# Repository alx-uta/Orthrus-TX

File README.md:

# Orthrus-TX

OrthrusTx is a custom high-performance RC transmitter platform built around the STM32H745 microcontroller and designed specifically for modern ExpressLRS-based systems. The project focuses on low-latency control, clean mixed-signal hardware design, modular RF integration, and long-term expandability without unnecessary complexity.

The hardware architecture separates critical analog, digital, and RF sections across an 8-layer PCB stackup to improve signal integrity and reduce noise coupling.

## Features

- STM32H745ZIT6 dual-core MCU
- Dual independent ExpressLRS interfaces
- Modular RF daughterboard design
- Precision filtered analog joystick inputs
- USB connectivity
- SD card support
- Rotary encoders and configurable inputs
- Dedicated analog and digital power domains
- Low-noise mixed-signal PCB layout
- Replaceable battery-oriented design

## Design Goals

OrthrusTx prioritizes:

- Low latency
- High reliability
- Electrical cleanliness
- Modular hardware architecture
- Repairability

## Project Vision

OrthrusTx is being developed both as a functional long-range RC transmitter and as a deep embedded hardware/software engineering project focused on performance, architecture, signal integrity, and system-level design.

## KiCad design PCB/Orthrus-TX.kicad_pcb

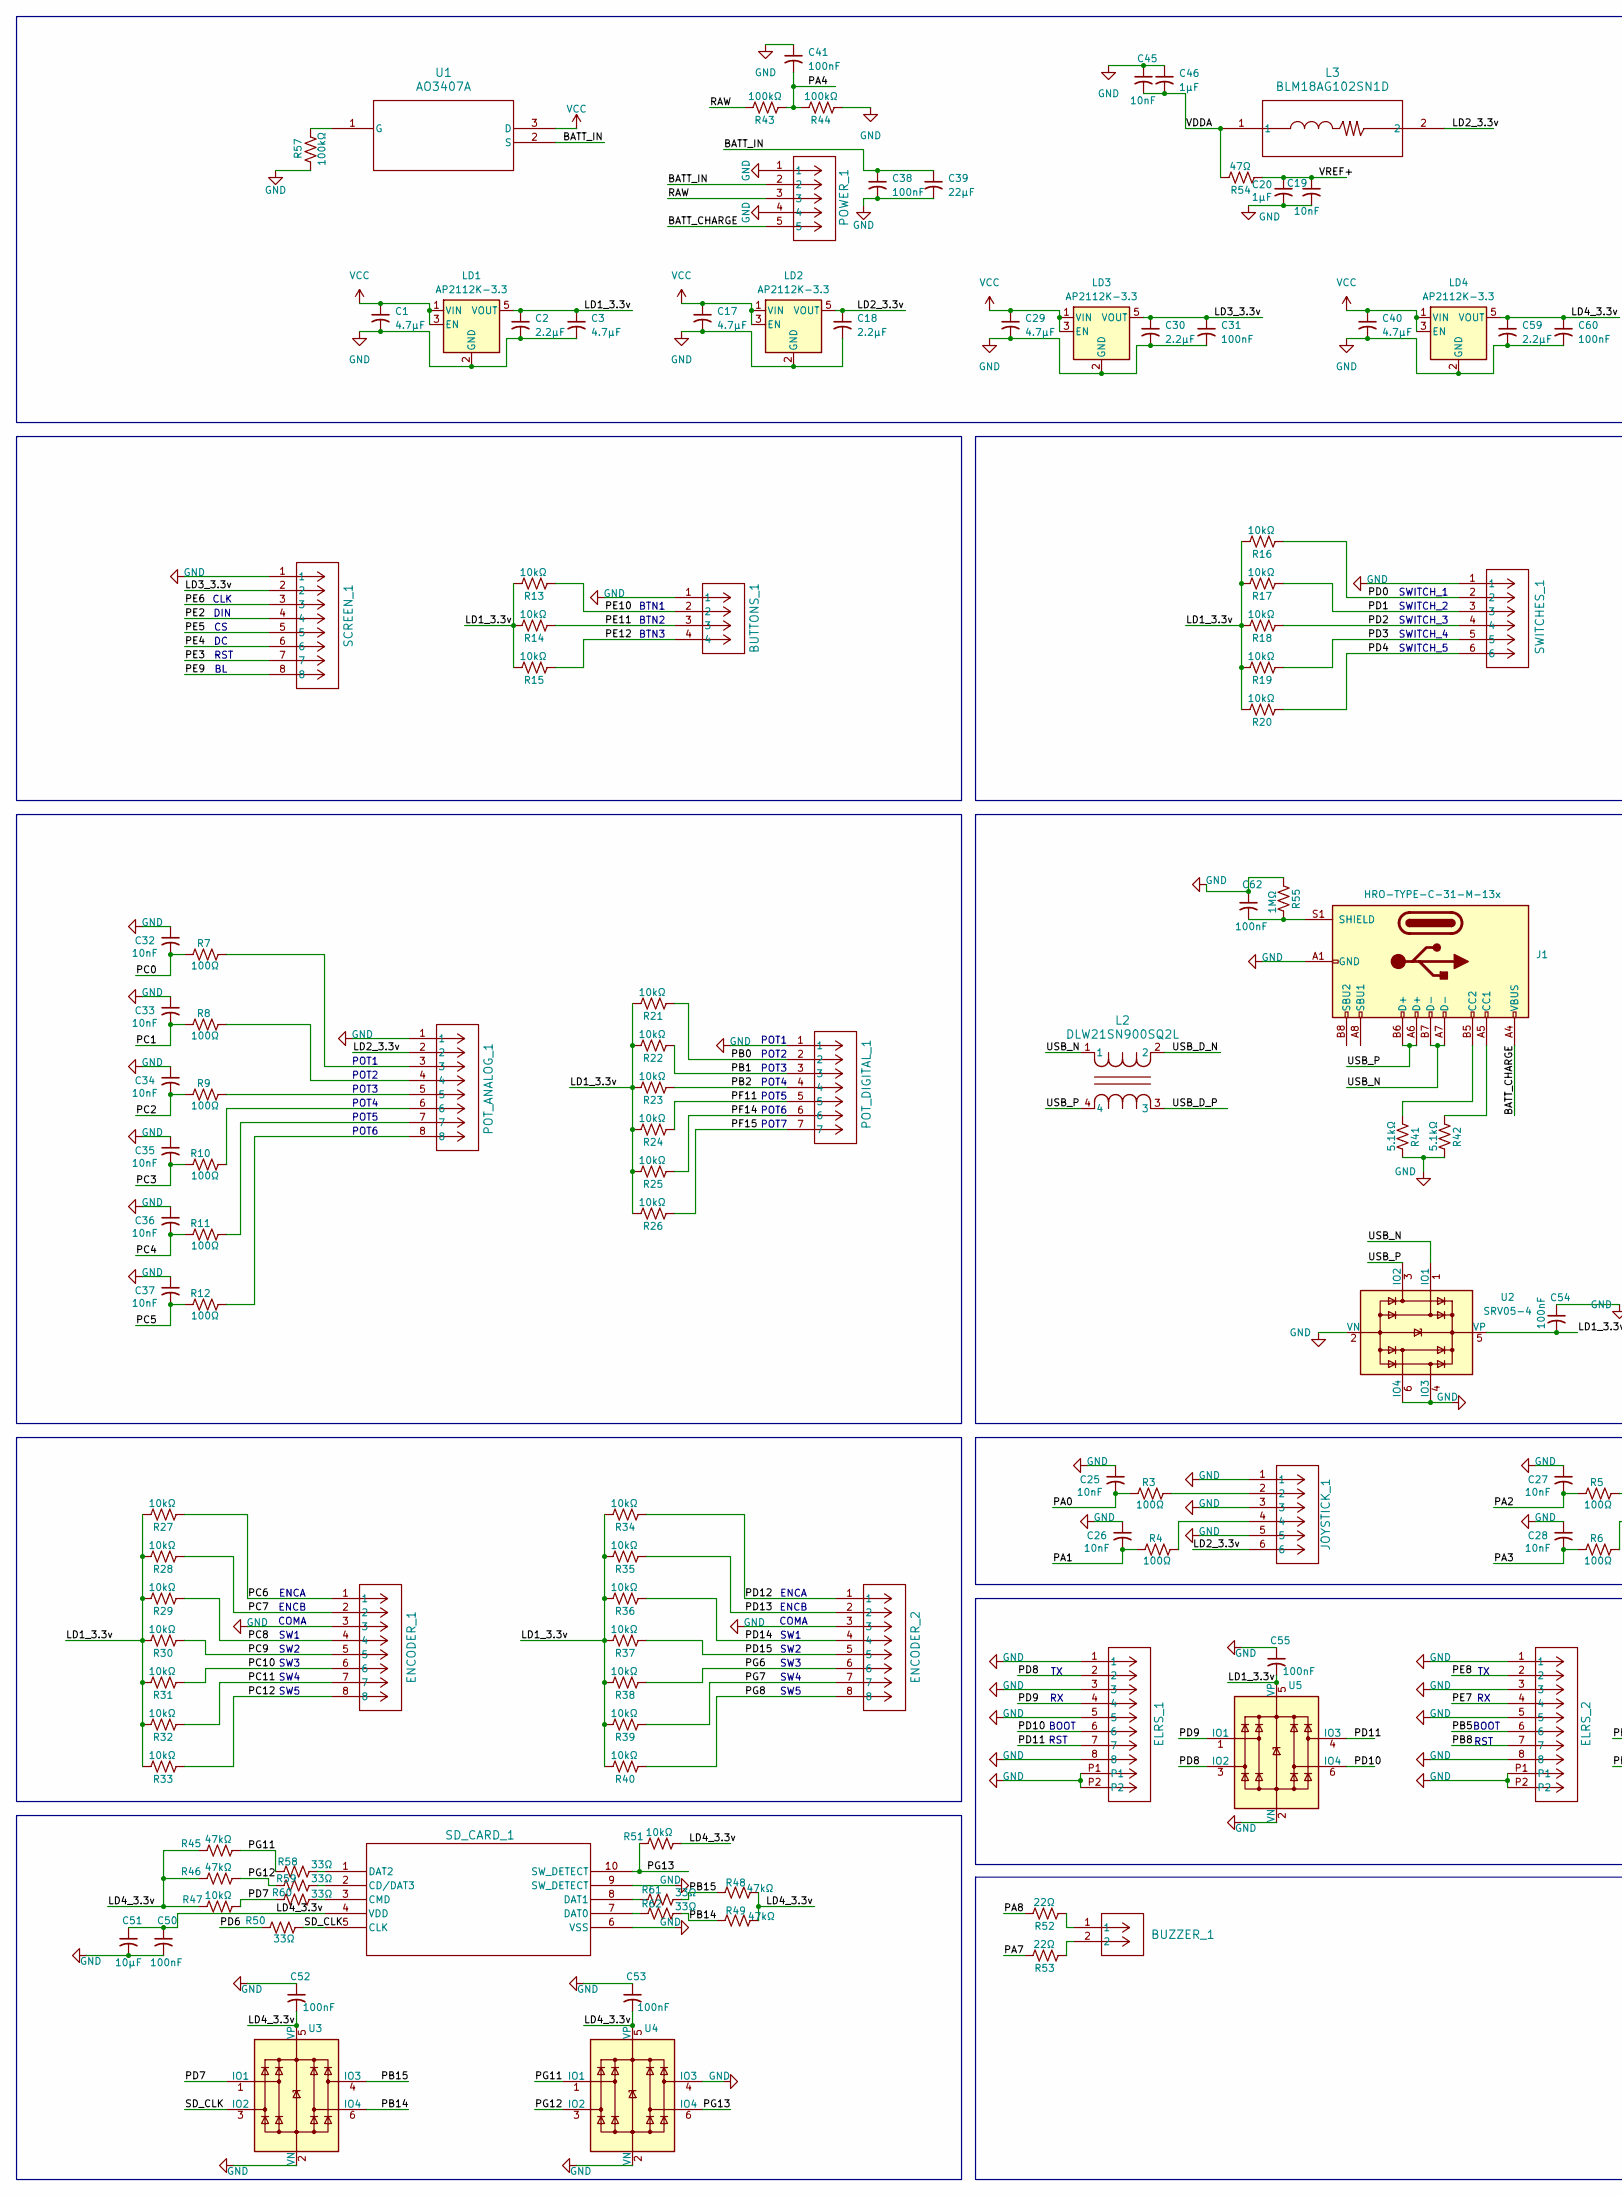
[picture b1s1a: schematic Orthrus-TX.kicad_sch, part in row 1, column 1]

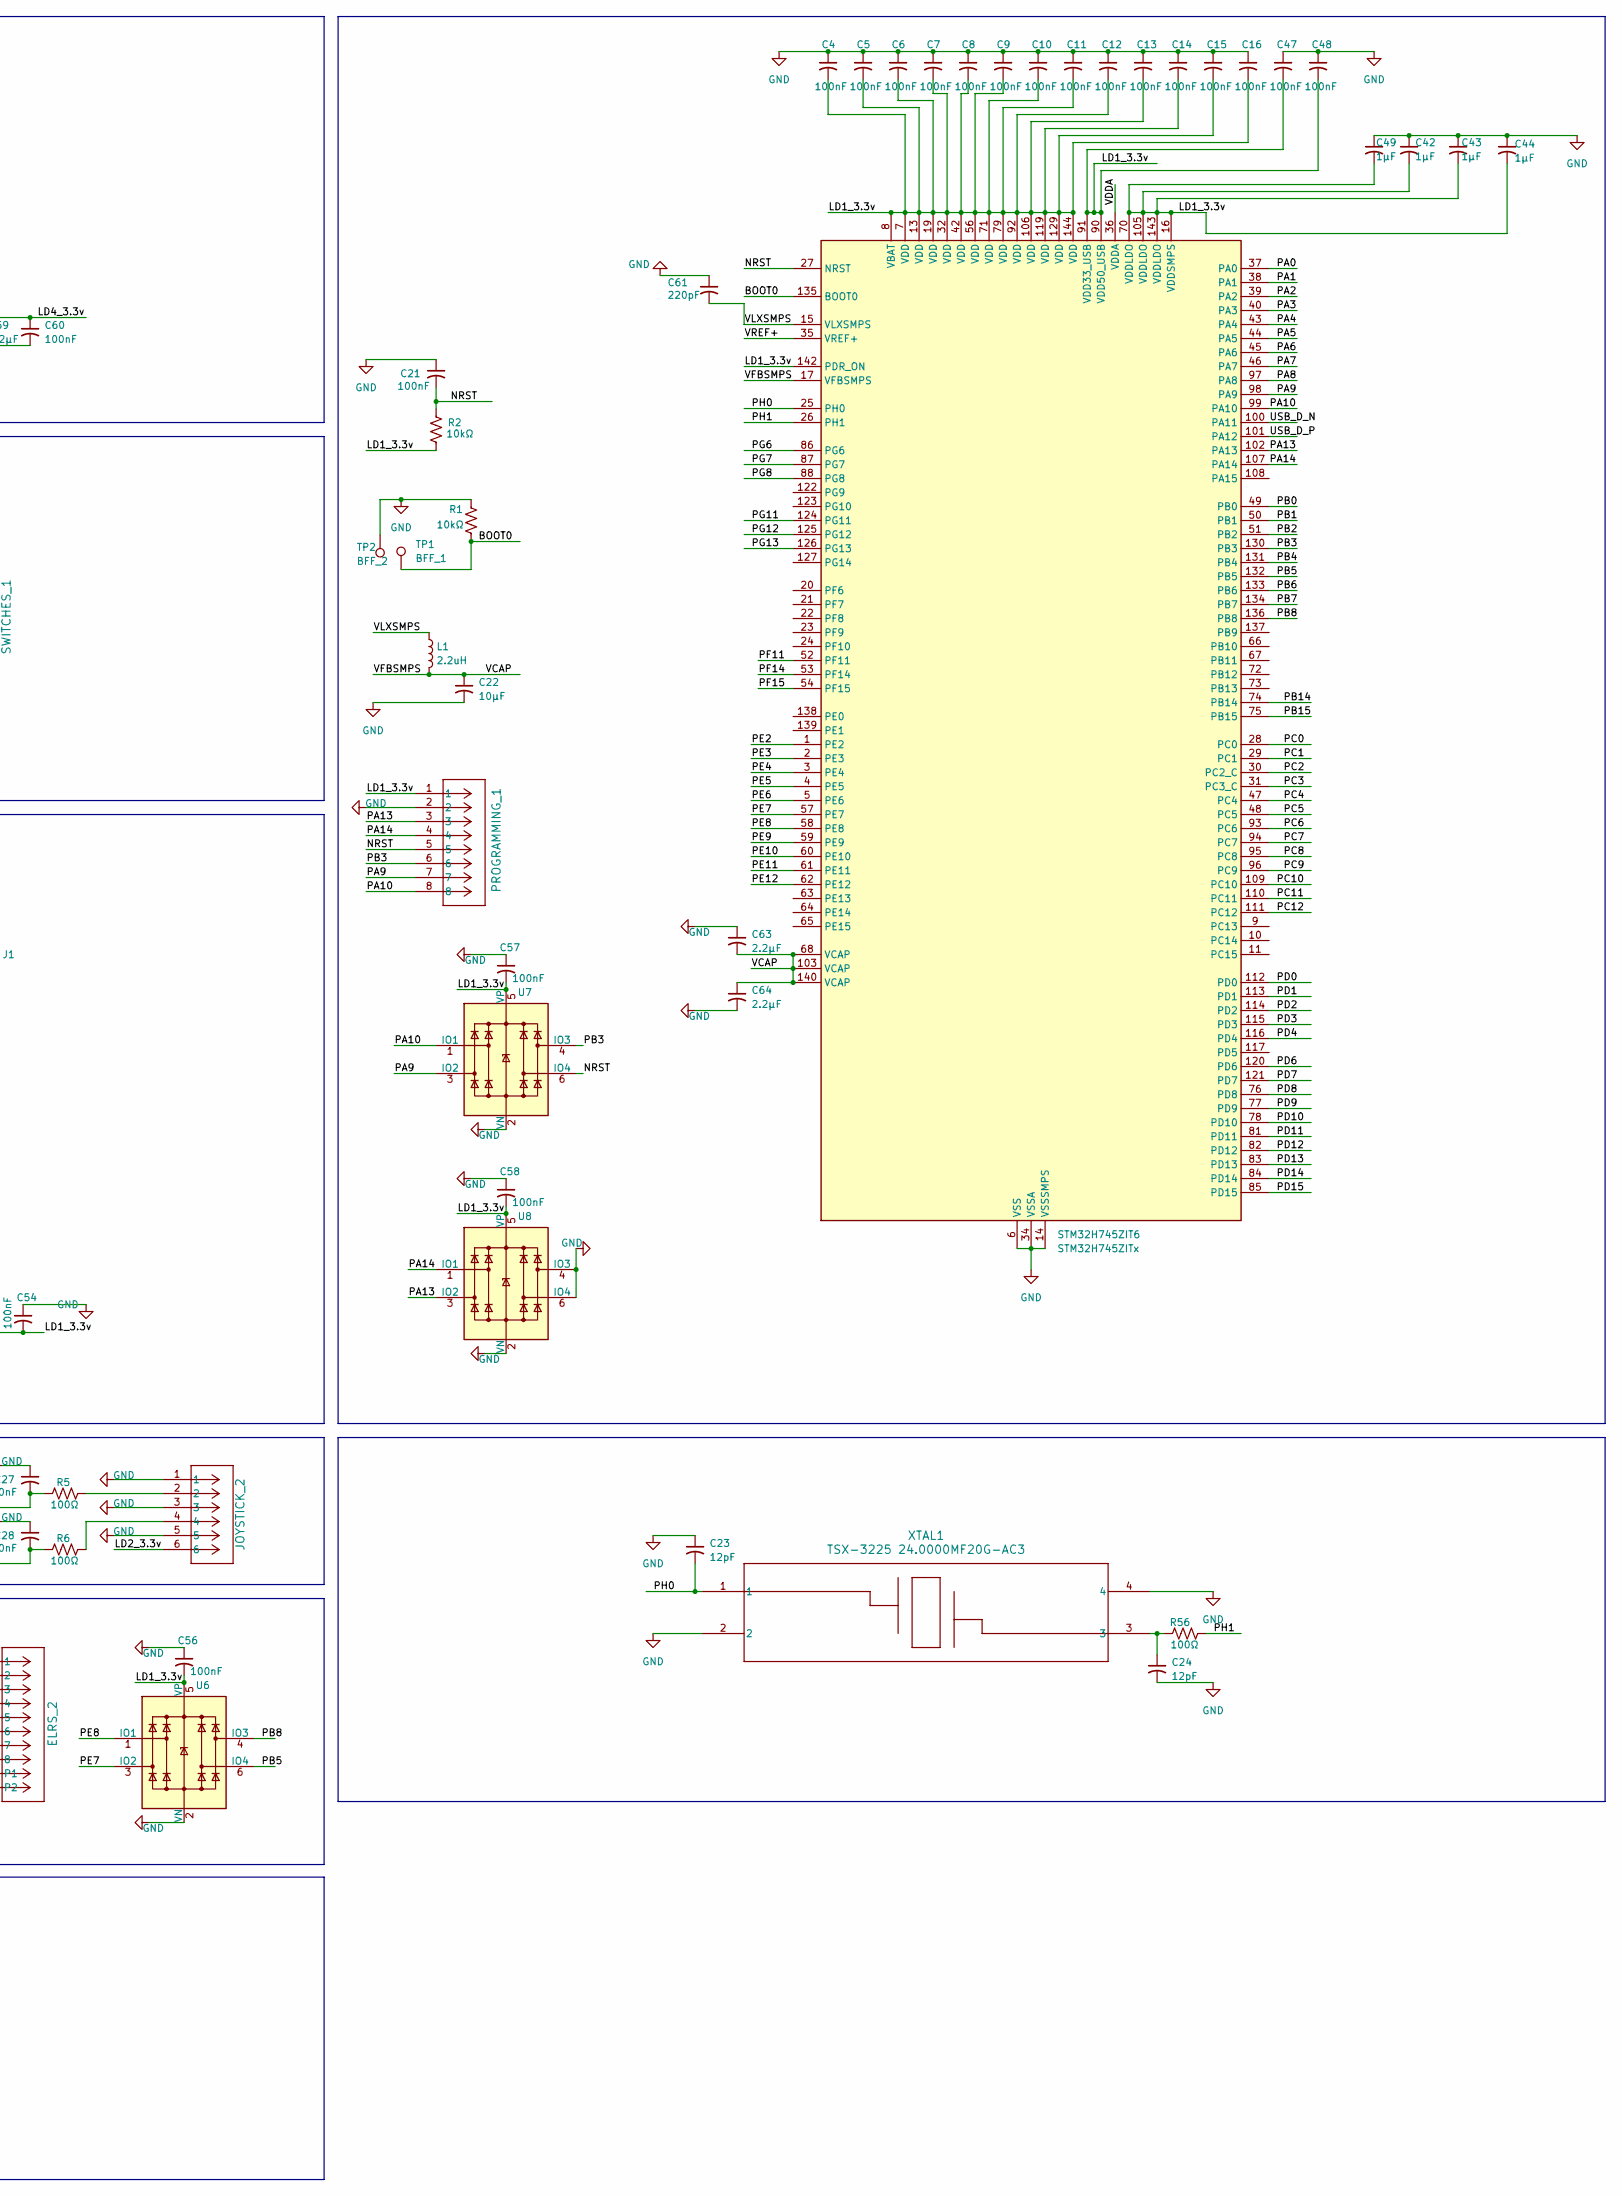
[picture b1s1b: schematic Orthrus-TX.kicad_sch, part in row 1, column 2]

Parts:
BUTTONS_1: 532610471; CONN_532610001-SD_04_MOL; LCSC C696092
BUZZER_1: 532610271; CONN_532610001-SD_02_MOL; LCSC C177225
C1, C3, C17, C29, C40: 4.7µF; C_0603_1608Metric; LCSC C19666
C2, C18, C30, C59, C63, C64: 2.2µF; C_0603_1608Metric; LCSC C23630
C4, C5, C6, C7, C8, C9, C10, C11, C12, C13, C14, C15, C16, C21, C31, C38, C41, C47, C48, C50, C52, C53, C54, C55, C56, C57, C58, C60, C62: 100nF; C_0603_1608Metric; LCSC C24452
C19, C25, C26, C27, C28, C32, C33, C34, C35, C36, C37, C45: 10nF; C_0603_1608Metric; LCSC C3836718
C20, C42, C43, C44, C46, C49: 1µF; C_0603_1608Metric; LCSC C2177011
C22, C51: 10µF; C_0603_1608Metric; LCSC C19702
C23, C24: 12pF; C_0603_1608Metric; LCSC C882527
C39: 22µF; C_0603_1608Metric; LCSC C2762594
C61: 220pF; C_0603_1608Metric; LCSC C882575
ELRS_1, ELRS_2: 5034800800; CON_5034800800_MOL; LCSC C293338
ENCODER_1, ENCODER_2: 532610871; CONN_532610001-SD_08_MOL; LCSC C293349
J1: HRO-TYPE-C-31-M-13x; Molex-216990_GCT-USB45xx_HRO-TYPE-C-31-M-13x-PiMicro_1_DOUB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; LCSC C963373
JOYSTICK_1, JOYSTICK_2: 532610671; CONN_532610001-SD_06_MOL; LCSC C17393620
L1: 2.2uH; L_0603_1608Metric; LCSC C48945021
L2: DLW21SN900SQ2L; IND_DLW21S_0805_MUR; LCSC C97856
L3: BLM18AG102SN1D; BLM18_MUR; LCSC C85824
LD1, LD2, LD3, LD4: AP2112K-3.3; SOT-23-5; LCSC C23380830
POT_ANALOG_1: 532610871; CONN_532610001-SD_08_MOL; LCSC C293349
POT_DIGITAL_1: 532610771; CONN_532610001-SD_07_MOL; LCSC C505276
POWER_1: 532610571; CONN_532610001-SD_05_MOL
PROGRAMMING_1: 532610871; CONN_532610001-SD_08_MOL; LCSC C293349
R1, R2, R13, R14, R15, R16, R17, R18, R19, R20, R21, R22, R23, R24, R25, R26, R27, R28, R29, R30, R31, R32, R33, R34, R35, R36, R37, R38, R39, R40, R47, R51: 10kΩ; R_0603_1608Metric; LCSC C95204
R3, R4, R5, R6, R7, R8, R9, R10, R11, R12, R56: 100Ω; R_0603_1608Metric; LCSC C122970
R41, R42: 5.1kΩ; R_0603_1608Metric; LCSC C122969
R43, R44, R57: 100kΩ; R_0603_1608Metric; LCSC C122538
R45, R46, R48, R49: 47kΩ; R_0603_1608Metric; LCSC C491223
R50, R58, R59, R60, R61, R62: 33Ω; R_0603_1608Metric; LCSC C403478
R52, R53: 22Ω; R_0603_1608Metric; LCSC C2907129
R54: 47Ω; R_0603_1608Metric; LCSC C403245
R55: 1MΩ; R_0603_1608Metric; LCSC C491226
SCREEN_1: 532610871; CONN_532610001-SD_08_MOL; LCSC C293349
SD_CARD_1: 1040310811; 104031-0811_MOL; LCSC C585350
STM32H745ZIT6: STM32H745ZITx; LQFP-144_20x20mm_P0.5mm; LCSC C730193
SWITCHES_1: 532610671; CONN_532610001-SD_06_MOL; LCSC C17393620
TP1: BFF_1; TestPoint_Pad_1.0x1.0mm
TP2: BFF_2; TestPoint_Pad_1.0x1.0mm
U1: AO3407A; SOT-23-3L_AOS; LCSC C15127
U2, U3, U4, U5, U6, U7, U8: SRV05-4; SOT-23-6; LCSC C558418
XTAL1: TSX-3225 24.0000MF20G-AC3; TSX-3225 24.0000MF20G-AC3_EPS; LCSC C2650460

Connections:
/BATT_CHARGE: J1.A4 (VBUS), J1.A9 (VBUS), J1.B4 (VBUS), J1.B9 (VBUS), POWER_1.5
/BATT_IN: C38.1, C39.1, POWER_1.2, U1.2 (S)
/BOOT0: R1.2, STM32H745ZIT6.135 (BOOT0), TP1.1 (1_1)
/LD1_3.3v: C2.1, C3.1, C4.2, C5.2, C6.2, C7.2, C8.2, C9.2, C10.2, C11.2, C12.2, C13.2, C14.2, C15.2, C16.2, C42.2, C43.2, C44.2, C47.2, C48.2, C49.2, C54.2, C55.2, C56.2, C57.2, C58.2, LD1.5 (VOUT), PROGRAMMING_1.1, R2.2, R13.2, R14.2, R15.2, R16.2, R17.2, R18.2, R19.2, R20.2, R21.2, R22.2, R23.2, R24.2, R25.2, R26.2, R27.2, R28.2, R29.2, R30.2, R31.2, R32.2, R33.2, R34.2, R35.2, R36.2, R37.2, R38.2, R39.2, R40.2, STM32H745ZIT6.7 (VDD), STM32H745ZIT6.8 (VBAT), STM32H745ZIT6.13 (VDD), STM32H745ZIT6.16 (VDDSMPS), STM32H745ZIT6.19 (VDD), STM32H745ZIT6.32 (VDD), STM32H745ZIT6.42 (VDD), STM32H745ZIT6.56 (VDD), STM32H745ZIT6.70 (VDDLDO), STM32H745ZIT6.71 (VDD), STM32H745ZIT6.79 (VDD), STM32H745ZIT6.90 (VDD50_USB), STM32H745ZIT6.91 (VDD33_USB), STM32H745ZIT6.92 (VDD), STM32H745ZIT6.105 (VDDLDO), STM32H745ZIT6.106 (VDD), STM32H745ZIT6.119 (VDD), STM32H745ZIT6.129 (VDD), STM32H745ZIT6.142 (PDR_ON), STM32H745ZIT6.143 (VDDLDO), STM32H745ZIT6.144 (VDD), U2.5 (VP), U5.5 (VP), U6.5 (VP), U7.5 (VP), U8.5 (VP)
/LD2_3.3v: C18.1, JOYSTICK_1.6, JOYSTICK_2.6, L3.2, LD2.5 (VOUT), POT_ANALOG_1.2
/LD3_3.3v: C30.1, C31.1, LD3.5 (VOUT), SCREEN_1.2
/LD4_3.3v: C50.1, C51.1, C52.2, C53.2, C59.1, C60.1, LD4.5 (VOUT), R45.2, R46.2, R47.2, R48.1, R49.1, R51.1, SD_CARD_1.4 (VDD), U3.5 (VP), U4.5 (VP)
/NRST: C21.2, PROGRAMMING_1.5, R2.1, STM32H745ZIT6.27 (NRST), U7.6 (IO4)
/PA0: C25.2, R3.1, STM32H745ZIT6.37 (PA0)
/PA1: C26.2, R4.1, STM32H745ZIT6.38 (PA1)
/PA2: C27.2, R5.1, STM32H745ZIT6.39 (PA2)
/PA3: C28.2, R6.1, STM32H745ZIT6.40 (PA3)
/PA4: C41.2, R43.2, R44.1, STM32H745ZIT6.43 (PA4)
/PA5: STM32H745ZIT6.44 (PA5)
/PA6: STM32H745ZIT6.45 (PA6)
/PA7: R53.1, STM32H745ZIT6.46 (PA7)
/PA8: R52.1, STM32H745ZIT6.97 (PA8)
/PA9: PROGRAMMING_1.7, STM32H745ZIT6.98 (PA9), U7.3 (IO2)
/PA10: PROGRAMMING_1.8, STM32H745ZIT6.99 (PA10), U7.1 (IO1)
/PA13: PROGRAMMING_1.3, STM32H745ZIT6.102 (PA13), U8.3 (IO2)
/PA14: PROGRAMMING_1.4, STM32H745ZIT6.107 (PA14), U8.1 (IO1)
/PB0: POT_DIGITAL_1.2, R21.1, STM32H745ZIT6.49 (PB0)
/PB1: POT_DIGITAL_1.3, R22.1, STM32H745ZIT6.50 (PB1)
/PB2: POT_DIGITAL_1.4, R23.1, STM32H745ZIT6.51 (PB2)
/PB3: PROGRAMMING_1.6, STM32H745ZIT6.130 (PB3), U7.4 (IO3)
/PB4: STM32H745ZIT6.131 (PB4)
/PB5: ELRS_2.6, STM32H745ZIT6.132 (PB5), U6.6 (IO4)
/PB6: STM32H745ZIT6.133 (PB6)
/PB7: STM32H745ZIT6.134 (PB7)
/PB8: ELRS_2.7, STM32H745ZIT6.136 (PB8), U6.4 (IO3)
/PB14: R49.2, R62.1, STM32H745ZIT6.74 (PB14), U3.6 (IO4)
/PB15: R48.2, R61.1, STM32H745ZIT6.75 (PB15), U3.4 (IO3)
/PC0: C32.2, R7.1, STM32H745ZIT6.28 (PC0)
/PC1: C33.2, R8.1, STM32H745ZIT6.29 (PC1)
/PC2: C34.2, R9.1, STM32H745ZIT6.30 (PC2_C)
/PC3: C35.2, R10.1, STM32H745ZIT6.31 (PC3_C)
/PC4: C36.2, R11.1, STM32H745ZIT6.47 (PC4)
/PC5: C37.2, R12.1, STM32H745ZIT6.48 (PC5)
/PC6: ENCODER_1.1, R27.1, STM32H745ZIT6.93 (PC6)
/PC7: ENCODER_1.2, R28.1, STM32H745ZIT6.94 (PC7)
/PC8: ENCODER_1.4, R29.1, STM32H745ZIT6.95 (PC8)
/PC9: ENCODER_1.5, R30.1, STM32H745ZIT6.96 (PC9)
/PC10: ENCODER_1.6, R31.1, STM32H745ZIT6.109 (PC10)
/PC11: ENCODER_1.7, R32.1, STM32H745ZIT6.110 (PC11)
/PC12: ENCODER_1.8, R33.1, STM32H745ZIT6.111 (PC12)
/PD0: R16.1, STM32H745ZIT6.112 (PD0), SWITCHES_1.2
/PD1: R17.1, STM32H745ZIT6.113 (PD1), SWITCHES_1.3
/PD2: R18.1, STM32H745ZIT6.114 (PD2), SWITCHES_1.4
/PD3: R19.1, STM32H745ZIT6.115 (PD3), SWITCHES_1.5
/PD4: R20.1, STM32H745ZIT6.116 (PD4), SWITCHES_1.6
/PD6: R50.2, STM32H745ZIT6.120 (PD6)
/PD7: R47.1, R60.2, STM32H745ZIT6.121 (PD7), U3.1 (IO1)
/PD8: ELRS_1.2, STM32H745ZIT6.76 (PD8), U5.3 (IO2)
/PD9: ELRS_1.4, STM32H745ZIT6.77 (PD9), U5.1 (IO1)
/PD10: ELRS_1.6, STM32H745ZIT6.78 (PD10), U5.6 (IO4)
/PD11: ELRS_1.7, STM32H745ZIT6.81 (PD11), U5.4 (IO3)
/PD12: ENCODER_2.1, R34.1, STM32H745ZIT6.82 (PD12)
/PD13: ENCODER_2.2, R35.1, STM32H745ZIT6.83 (PD13)
/PD14: ENCODER_2.4, R36.1, STM32H745ZIT6.84 (PD14)
/PD15: ENCODER_2.5, R37.1, STM32H745ZIT6.85 (PD15)
/PE2: SCREEN_1.4, STM32H745ZIT6.1 (PE2)
/PE3: SCREEN_1.7, STM32H745ZIT6.2 (PE3)
/PE4: SCREEN_1.6, STM32H745ZIT6.3 (PE4)
/PE5: SCREEN_1.5, STM32H745ZIT6.4 (PE5)
/PE6: SCREEN_1.3, STM32H745ZIT6.5 (PE6)
/PE7: ELRS_2.4, STM32H745ZIT6.57 (PE7), U6.3 (IO2)
/PE8: ELRS_2.2, STM32H745ZIT6.58 (PE8), U6.1 (IO1)
/PE9: SCREEN_1.8, STM32H745ZIT6.59 (PE9)
/PE10: BUTTONS_1.2, R13.1, STM32H745ZIT6.60 (PE10)
/PE11: BUTTONS_1.3, R14.1, STM32H745ZIT6.61 (PE11)
/PE12: BUTTONS_1.4, R15.1, STM32H745ZIT6.62 (PE12)
/PF11: POT_DIGITAL_1.5, R24.1, STM32H745ZIT6.52 (PF11)
/PF14: POT_DIGITAL_1.6, R25.1, STM32H745ZIT6.53 (PF14)
/PF15: POT_DIGITAL_1.7, R26.1, STM32H745ZIT6.54 (PF15)
/PG6: ENCODER_2.6, R38.1, STM32H745ZIT6.86 (PG6)
/PG7: ENCODER_2.7, R39.1, STM32H745ZIT6.87 (PG7)
/PG8: ENCODER_2.8, R40.1, STM32H745ZIT6.88 (PG8)
/PG11: R45.1, R58.2, STM32H745ZIT6.124 (PG11), U4.1 (IO1)
/PG12: R46.1, R59.2, STM32H745ZIT6.125 (PG12), U4.3 (IO2)
/PG13: R51.2, SD_CARD_1.10 (SW_DETECT), STM32H745ZIT6.126 (PG13), U4.6 (IO4)
/PH0: C23.2, STM32H745ZIT6.25 (PH0), XTAL1.1
/PH1: R56.2, STM32H745ZIT6.26 (PH1)
/RAW: POWER_1.3, R43.1
/SD_CLK: R50.1, SD_CARD_1.5 (CLK), U3.3 (IO2)
/USB_D_N: L2.2, STM32H745ZIT6.100 (PA11)
/USB_D_P: L2.3, STM32H745ZIT6.101 (PA12)
/USB_N: J1.A7 (D-), J1.B7 (D-), L2.1, U2.1 (IO1)
/USB_P: J1.A6 (D+), J1.B6 (D+), L2.4, U2.3 (IO2)
/VCAP: C22.1, C63.2, C64.1, L1.2, STM32H745ZIT6.17 (VFBSMPS), STM32H745ZIT6.68 (VCAP), STM32H745ZIT6.103 (VCAP), STM32H745ZIT6.140 (VCAP)
/VDDA: C45.2, C46.2, L3.1, R54.1, STM32H745ZIT6.36 (VDDA)
/VLXSMPS: C61.2, L1.1, STM32H745ZIT6.15 (VLXSMPS)
/VREF+: C19.1, C20.1, R54.2, STM32H745ZIT6.35 (VREF+)
GND: BUTTONS_1.1, C1.2, C2.2, C3.2, C4.1, C5.1, C6.1, C7.1, C8.1, C9.1, C10.1, C11.1, C12.1, C13.1, C14.1, C15.1, C16.1, C17.2, C18.2, C19.2, C20.2, C21.1, C22.2, C23.1, C24.2, C25.1, C26.1, C27.1, C28.1, C29.2, C30.2, C31.2, C32.1, C33.1, C34.1, C35.1, C36.1, C37.1, C38.2, C39.2, C40.2, C41.1, C42.1, C43.1, C44.1, C45.1, C46.1, C47.1, C48.1, C49.1, C50.2, C51.2, C52.1, C53.1, C54.1, C55.1, C56.1, C57.1, C58.1, C59.2, C60.2, C61.1, C62.1, C63.1, C64.2, ELRS_1.1, ELRS_1.3, ELRS_1.5, ELRS_1.8, ELRS_1.P1, ELRS_1.P2, ELRS_2.1, ELRS_2.3, ELRS_2.5, ELRS_2.8, ELRS_2.P1, ELRS_2.P2, ENCODER_1.3, ENCODER_2.3, J1.A1 (GND), J1.A12 (GND), J1.B1 (GND), J1.B12 (GND), JOYSTICK_1.1, JOYSTICK_1.3, JOYSTICK_1.5, JOYSTICK_2.1, JOYSTICK_2.3, JOYSTICK_2.5, LD1.2 (GND), LD2.2 (GND), LD3.2 (GND), LD4.2 (GND), POT_ANALOG_1.1, POT_DIGITAL_1.1, POWER_1.1, POWER_1.4, PROGRAMMING_1.2, R1.1, R41.2, R42.2, R44.2, R55.1, R57.2, SCREEN_1.1, SD_CARD_1.6 (VSS), SD_CARD_1.9 (SW_DETECT), STM32H745ZIT6.6 (VSS), STM32H745ZIT6.12 (VSS), STM32H745ZIT6.14 (VSSSMPS), STM32H745ZIT6.18 (VSS), STM32H745ZIT6.33 (VSS), STM32H745ZIT6.34 (VSSA), STM32H745ZIT6.41 (VSS), STM32H745ZIT6.55 (VSS), STM32H745ZIT6.69 (VSS), STM32H745ZIT6.80 (VSS), STM32H745ZIT6.89 (VSS), STM32H745ZIT6.104 (VSS), STM32H745ZIT6.118 (VSS), STM32H745ZIT6.128 (VSS), STM32H745ZIT6.141 (VSS), SWITCHES_1.1, TP2.1 (1_1), U2.2 (VN), U2.4 (IO3), U2.6 (IO4), U3.2 (VN), U4.2 (VN), U4.4 (IO3), U5.2 (VN), U6.2 (VN), U7.2 (VN), U8.2 (VN), U8.4 (IO3), U8.6 (IO4), XTAL1.2, XTAL1.4
unnamed: BUZZER_1.1, R52.2
unnamed: BUZZER_1.2, R53.2
unnamed: C24.1, R56.1, XTAL1.3
unnamed: J1.A5 (CC1), R42.1
unnamed: J1.B5 (CC2), R41.1
unnamed: C62.2, J1.S1 (SHIELD), R55.2
unnamed: JOYSTICK_1.2, R3.2
unnamed: JOYSTICK_1.4, R4.2
unnamed: JOYSTICK_2.2, R5.2
unnamed: JOYSTICK_2.4, R6.2
unnamed: POT_ANALOG_1.3, R7.2
unnamed: POT_ANALOG_1.4, R8.2
unnamed: POT_ANALOG_1.5, R9.2
unnamed: POT_ANALOG_1.6, R10.2
unnamed: POT_ANALOG_1.7, R11.2
unnamed: POT_ANALOG_1.8, R12.2
unnamed: R59.1, SD_CARD_1.2 (CD/DAT3)
unnamed: R60.1, SD_CARD_1.3 (CMD)
unnamed: R62.2, SD_CARD_1.7 (DAT0)
unnamed: R61.2, SD_CARD_1.8 (DAT1)
unnamed: R58.1, SD_CARD_1.1 (DAT2)
unnamed: R57.1, U1.1 (G)
VCC: C1.1, C17.1, C29.1, C40.1, LD1.1 (VIN), LD1.3 (EN), LD2.1 (VIN), LD2.3 (EN), LD3.1 (VIN), LD3.3 (EN), LD4.1 (VIN), LD4.3 (EN), U1.3 (D)

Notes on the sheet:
SWITCH_3
SW1
ENCB
POT3
POT1
SW5
RST
SWITCH_1
SWITCH_4
SW3
COMA
CLK
POT2
ENCA
POT7
BOOT
BTN2
SW4
POT4
BTN3
DIN
POT5
POT6
SWITCH_2
SW2
BTN1
SWITCH_5

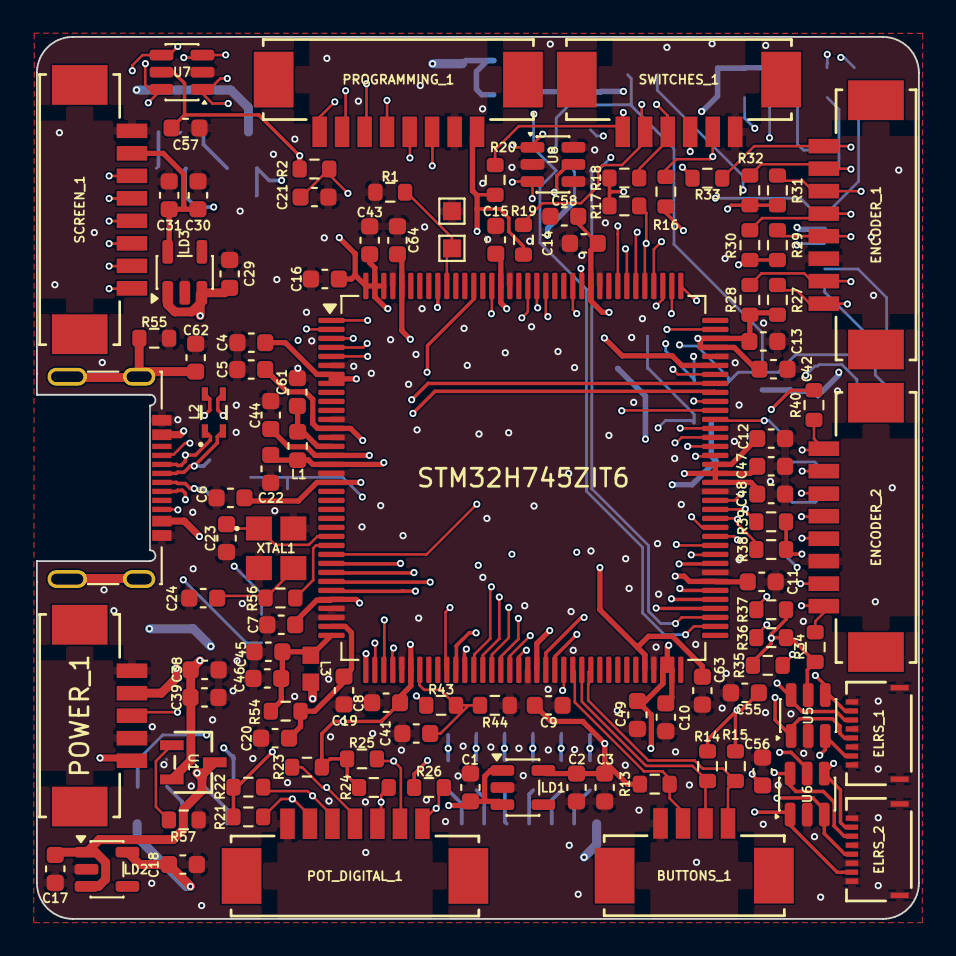
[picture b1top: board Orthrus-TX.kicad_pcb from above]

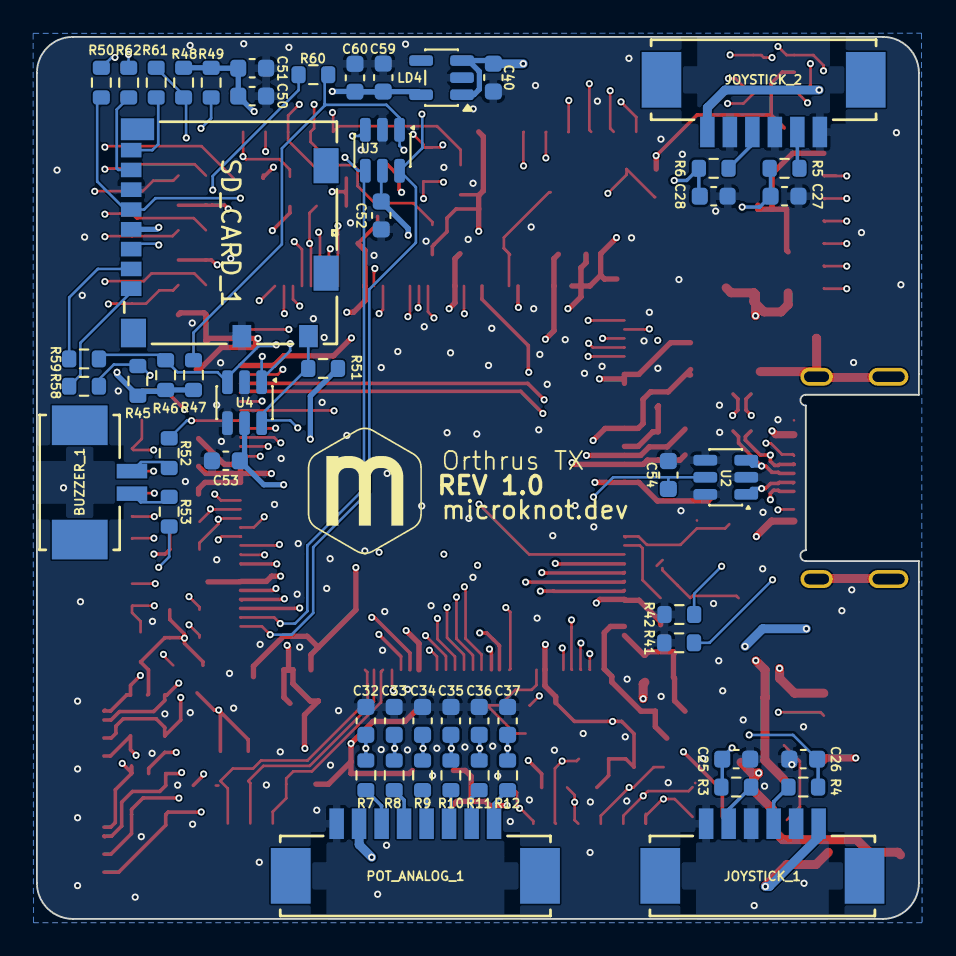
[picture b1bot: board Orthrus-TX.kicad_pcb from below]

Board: 8 copper layers, 49.0 x 49.0 mm, 162 parts (54 on the bottom side), 111 nets.

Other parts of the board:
Orthrus TX: REV 1.0; TX-Logo

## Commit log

2026-05-15 Project details
2026-05-15 v1.0.0
2026-05-16 DRC update
2026-05-16 DRU updates
2026-05-16 pcb update
2026-05-16 extra GND vias
2026-05-16 adjust the USB traces
2026-05-16 small adjustment for the logo
2026-05-16 change signal order for joysticks
2026-05-17 add SRV05-4 for ELRS
2026-05-17 add SRV05-4 for programming/debugging
2026-05-21 Use Thermal Reliefs for L1 and L8
2026-05-21 extra LDO for the SDCard
2026-05-23 schematic/net update
2026-05-27 sd card routing update
2026-05-31 data update
2026-06-06 add ul_532610571
